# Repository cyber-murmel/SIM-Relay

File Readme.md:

# SIM Relay
This is an approach of routing SIM card communication through a computer network. The project is based on [Ladyada's SIM reader](http://www.ladyada.net/make/simreader/)
## The Hardware
The printed circuit board is designed with surface mount parts only and measures 25.43x20.32 mm (1.00x0.80 inches). It only consist of a hex inverter, a crystal, some passives, a LED, the SIM card slot and pads to connect to an USB-UART converter. All passives and the LED are in a 0603 package.

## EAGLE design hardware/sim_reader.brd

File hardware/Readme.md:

#Description
The board fullfills two tasks: Making the SIM card run by proving a clock and adapting the RX and TX signal of the UART to the one I/O line of the SIM card (transmit and receive to transceive).
The first part is done by connecting the in- and outputs of an inverter over a crystal that resonates with the desired frequency. This is stabilized by some passive components and then buffered by another inverter.
The transceiver part is done for the once direction by connecting the I/O line of the SIM card to the RX of the USB-UART converter. For the other direction, we pull up the I/O line by a resistor and connect the TX of the USB-UART converter through an inverter to a transistor, that can pull the line down (thereby the signal is double inverted).
Doing so, we prevent short circuiting that could occure if e.g. the SIM card pulls up and the USB-UART pulls down.
#Getting your own
I have the board uploaded to [OSH Park](https://oshpark.com/shared_projects/abhypSsD) if you want to order some.

|Part(s) |Value |
|---|---|
| C1, C2 | according to crystal (e.g. 15pF) |
| C3 | 1uF |
| C4 | 100uF |
| IC1 | 74AC04D |
| Q1 | NPN SOT23 BEC (e.g. MMBT2222A) |
| R1 | 1 Meg |
| R2, R3 | 1K |
| R4, R5 | 10K |
| SIM1| C707-10M006-136-2 |
| X1 | 3.686 MHz|

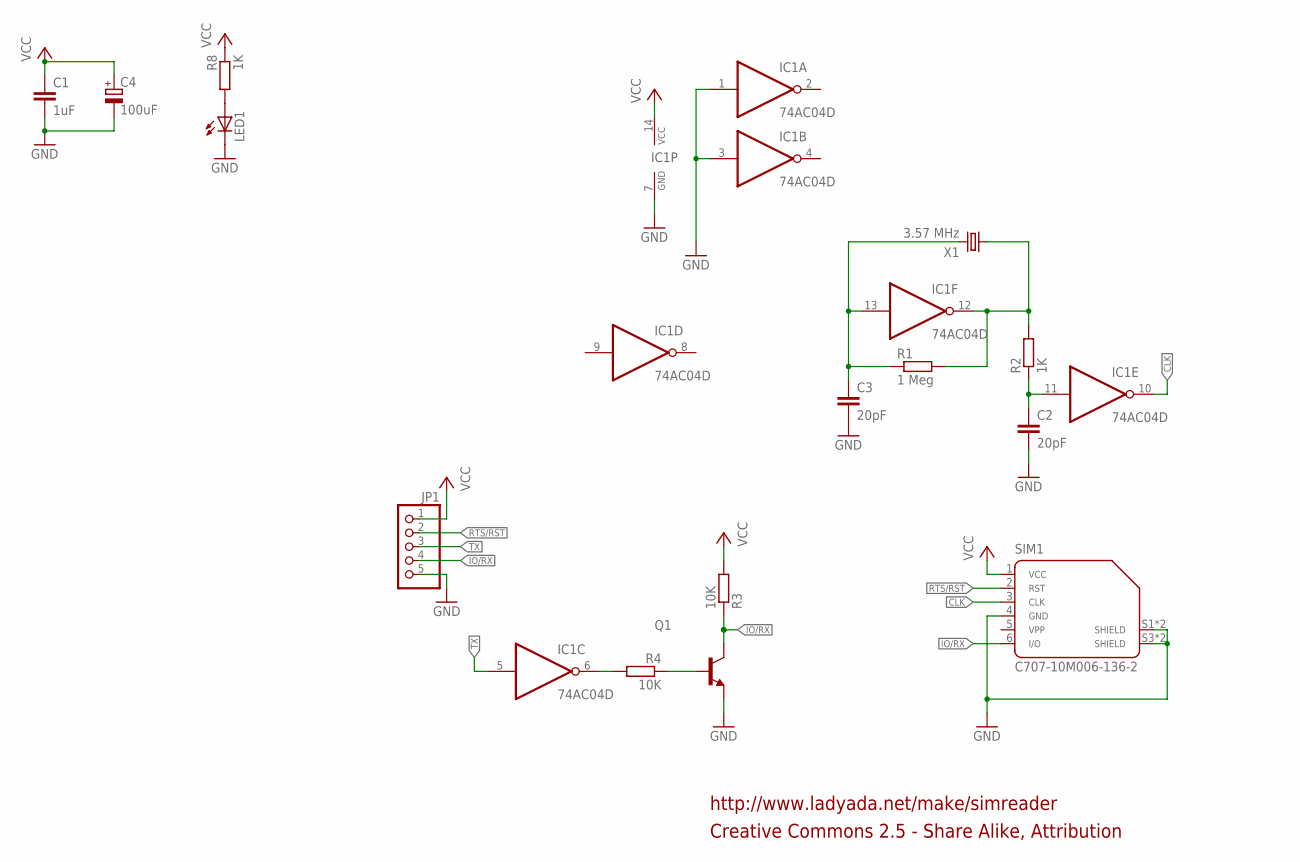
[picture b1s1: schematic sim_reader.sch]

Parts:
C1: 1uF; C0805
C2, C3: 20pF; C0805
C4: 100uF; 140CLH-0810
IC1: 74AC04D; SO14
JP1: PINHD-1X5; 1X05
LED1: LEDCHIPLED_0805; CHIPLED_0805
Q1: BC808-NPN-SOT23-BEC; SOT23-BEC
R1: 1 Meg; R0805
R2, R8: 1K; R0805
R3, R4: 10K; R0805
SIM1: C707-10M006-136-2; C707_10M006_136_2
X1: 3.57 MHz; HC49UP

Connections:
CLK: IC1.10 (O), SIM1.3
GND: C1.2, C2.2, C3.2, C4.-, IC1.1 (I), IC1.3 (I), IC1.7 (GND), JP1.5, LED1.C, Q1.E, SIM1.4, SIM1.S1, SIM1.S2 (S1), SIM1.S3 (S2), SIM1.S4 (S2)
IO/RX: JP1.4, Q1.C, R3.1, SIM1.6
unnamed: C3.1, IC1.13 (I), R1.1, X1.2
unnamed: IC1.12 (O), R1.2, R2.2, X1.1
unnamed: C2.1, IC1.11 (I), R2.1
unnamed: IC1.6 (O), R4.2
unnamed: Q1.B, R4.1
unnamed: LED1.A, R8.2
RTS/RST: JP1.2, SIM1.2
TX: IC1.5 (I), JP1.3
VCC: C1.1, C4.+, IC1.14 (VCC), JP1.1, R3.2, R8.1, SIM1.1

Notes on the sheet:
Creative Commons 2.5 - Share Alike, Attribution
http://www.ladyada.net/make/simreader

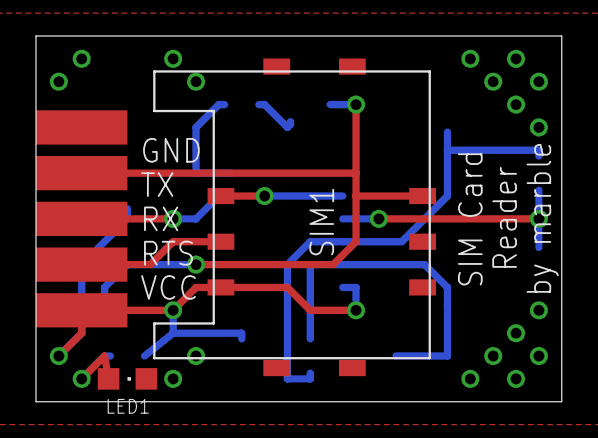
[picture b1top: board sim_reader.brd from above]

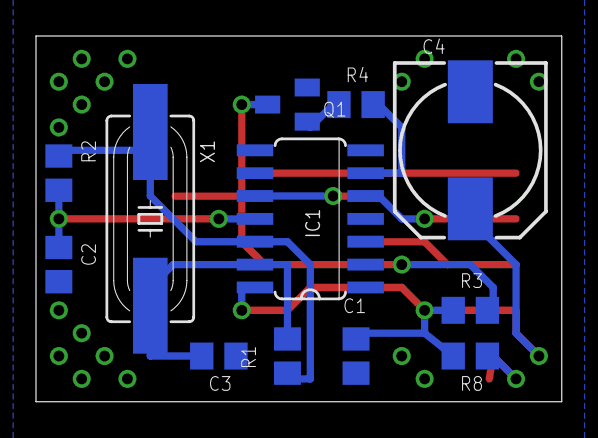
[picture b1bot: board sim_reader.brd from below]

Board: 2 copper layers, 29.2 x 20.3 mm, 15 parts (12 on the bottom side), 12 nets.

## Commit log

2016-10-14 added hardware files
2016-10-19 added readme
2016-10-19 redisgned. now compatible to most USB UART converters; very small
2016-10-19 added images
2016-10-19 used images
2016-10-19 added OSH Park link
2016-10-19 add hardware explanation
2016-10-19 Create LICENCE
2016-10-19 Create HACKERETHICS
2016-10-19 Created Readme.md
2016-10-19 added hardware description
2016-10-25 minor changes;
    nicer sentences (I know words. I know the best words.)
    errata
2016-10-26 added boards with ftdi chip
